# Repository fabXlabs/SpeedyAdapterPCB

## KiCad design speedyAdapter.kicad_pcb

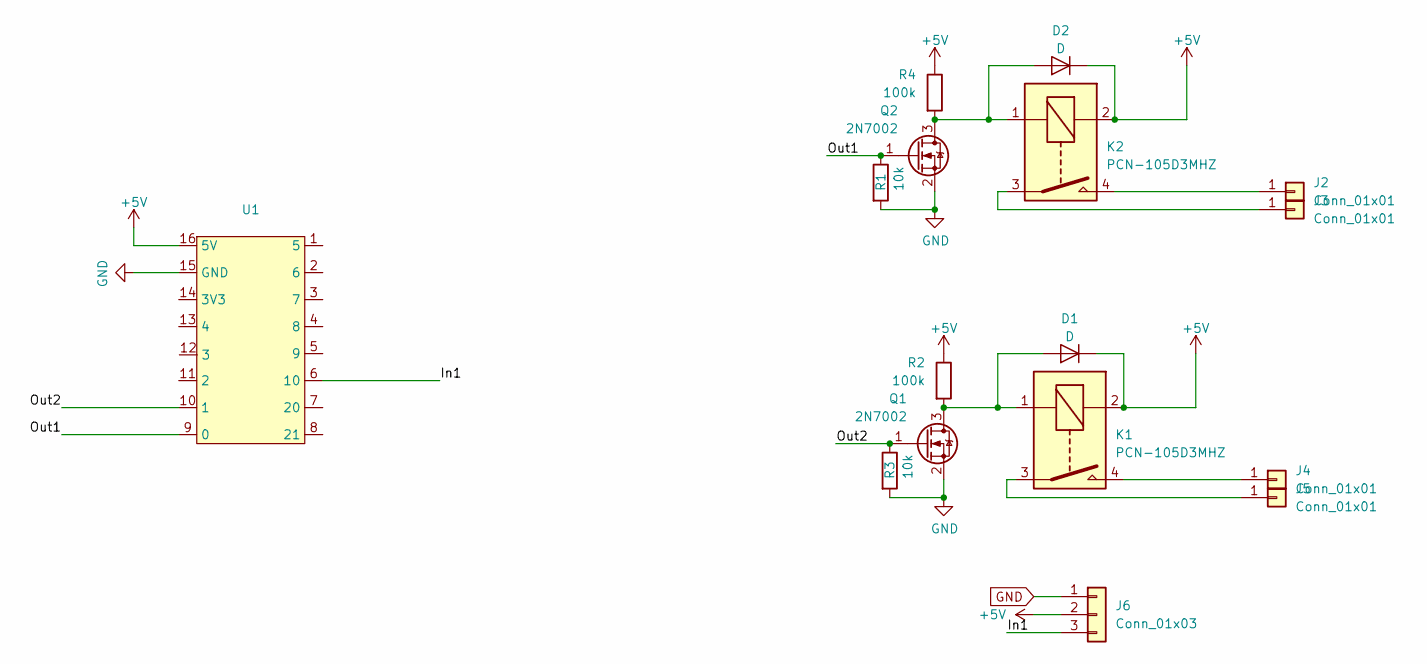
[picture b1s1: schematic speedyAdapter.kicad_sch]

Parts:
D1, D2: D; D_SOD-123; Farnell# 2760409
J2, J3, J4, J5: Conn_01x01; Pin_D1.4mm_L8.5mm_W2.8mm_FlatFork
J6: Conn_01x03; PinSocket_1x03_P2.54mm_Vertical
K1, K2: PCN-105D3MHZ; Relay_SPST_TE_PCN-1xxD3MHZ; Farnell# 4444930
Q1, Q2: 2N7002; SOT-23; Farnell# 3924478
R1, R3: 10k; R_0603_1608Metric; Farnell# 3495224
R2, R4: 100k; R_0603_1608Metric; Farnell# 3495222
U1: esp32-c3 supermini

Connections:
+5V: D1.1 (K), D2.1 (K), J6.2, K1.2, K2.2, R2.1, R4.1, U1.16 (5V)
/In1: J6.3, U1.6 (10)
/Out1: Q2.1 (G), R1.1, U1.9 (0)
/Out2: Q1.1 (G), R3.1, U1.10 (1)
GND: J6.1, Q1.2 (S), Q2.2 (S), R1.2, R3.2, U1.15 (GND)
unnamed: D1.2 (A), K1.1, Q1.3 (D), R2.2
unnamed: D2.2 (A), K2.1, Q2.3 (D), R4.2
unnamed: J2.1, K2.4
unnamed: J3.1, K2.3
unnamed: J4.1, K1.4
unnamed: J5.1, K1.3

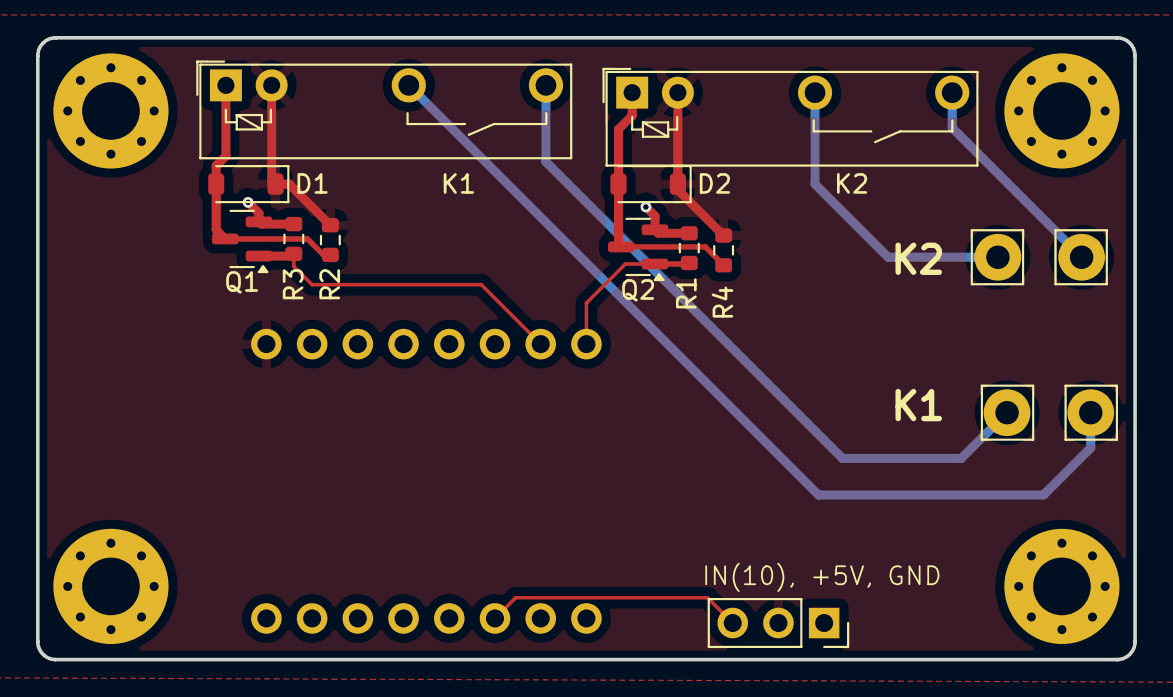
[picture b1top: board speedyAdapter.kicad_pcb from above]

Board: 2 copper layers, 61.0 x 34.5 mm, 16 parts (0 on the bottom side), 11 nets.

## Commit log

2025-02-28 speedy to fabx Adapter
